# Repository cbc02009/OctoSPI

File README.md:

# OctoSPI
SPI breakout board for the BTT Octopus

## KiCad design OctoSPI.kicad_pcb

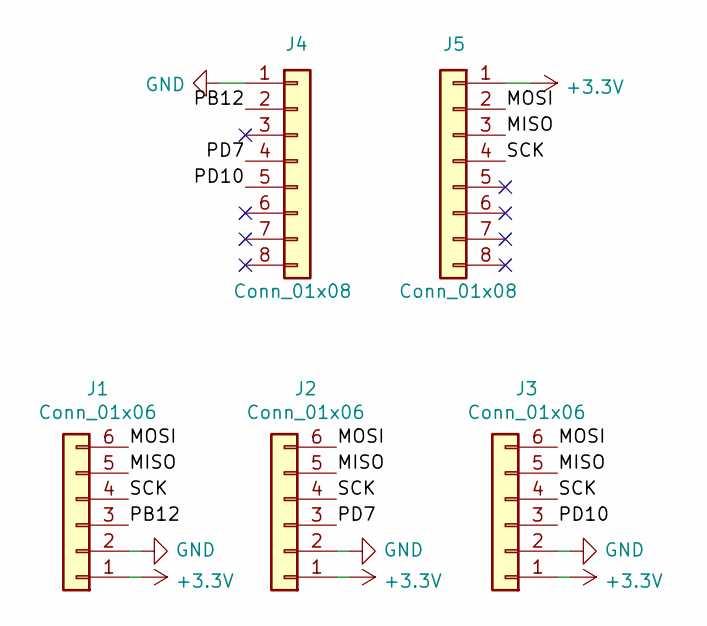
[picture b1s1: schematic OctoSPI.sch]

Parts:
J1, J2, J3: Conn_01x06; JST_PH_B6B-PH-K_1x06_P2.00mm_Vertical
J4, J5: Conn_01x08; PinHeader_1x08_P2.54mm_Vertical

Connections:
+3V3: J1.1, J2.1, J3.1, J5.1
/MISO: J1.5, J2.5, J3.5, J5.3
/MOSI: J1.6, J2.6, J3.6, J5.2
/PB12: J1.3, J4.2
/PD7: J2.3, J4.4
/PD10: J3.3, J4.5
/SCK: J1.4, J2.4, J3.4, J5.4
GND: J1.2, J2.2, J3.2, J4.1

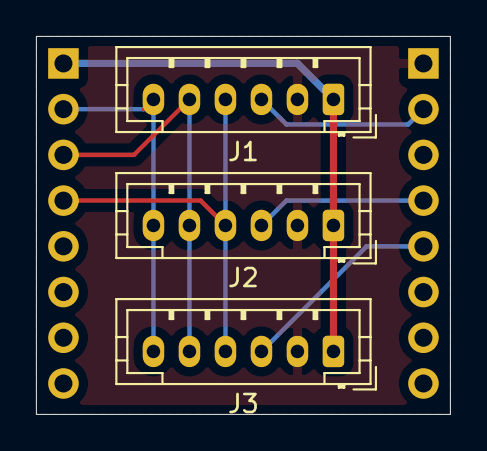
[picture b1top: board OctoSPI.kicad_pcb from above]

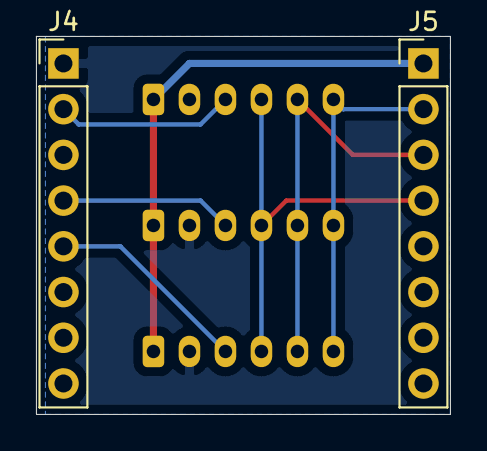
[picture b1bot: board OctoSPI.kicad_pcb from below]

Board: 2 copper layers, 23.0 x 21.0 mm, 5 parts (2 on the bottom side), 8 nets.
